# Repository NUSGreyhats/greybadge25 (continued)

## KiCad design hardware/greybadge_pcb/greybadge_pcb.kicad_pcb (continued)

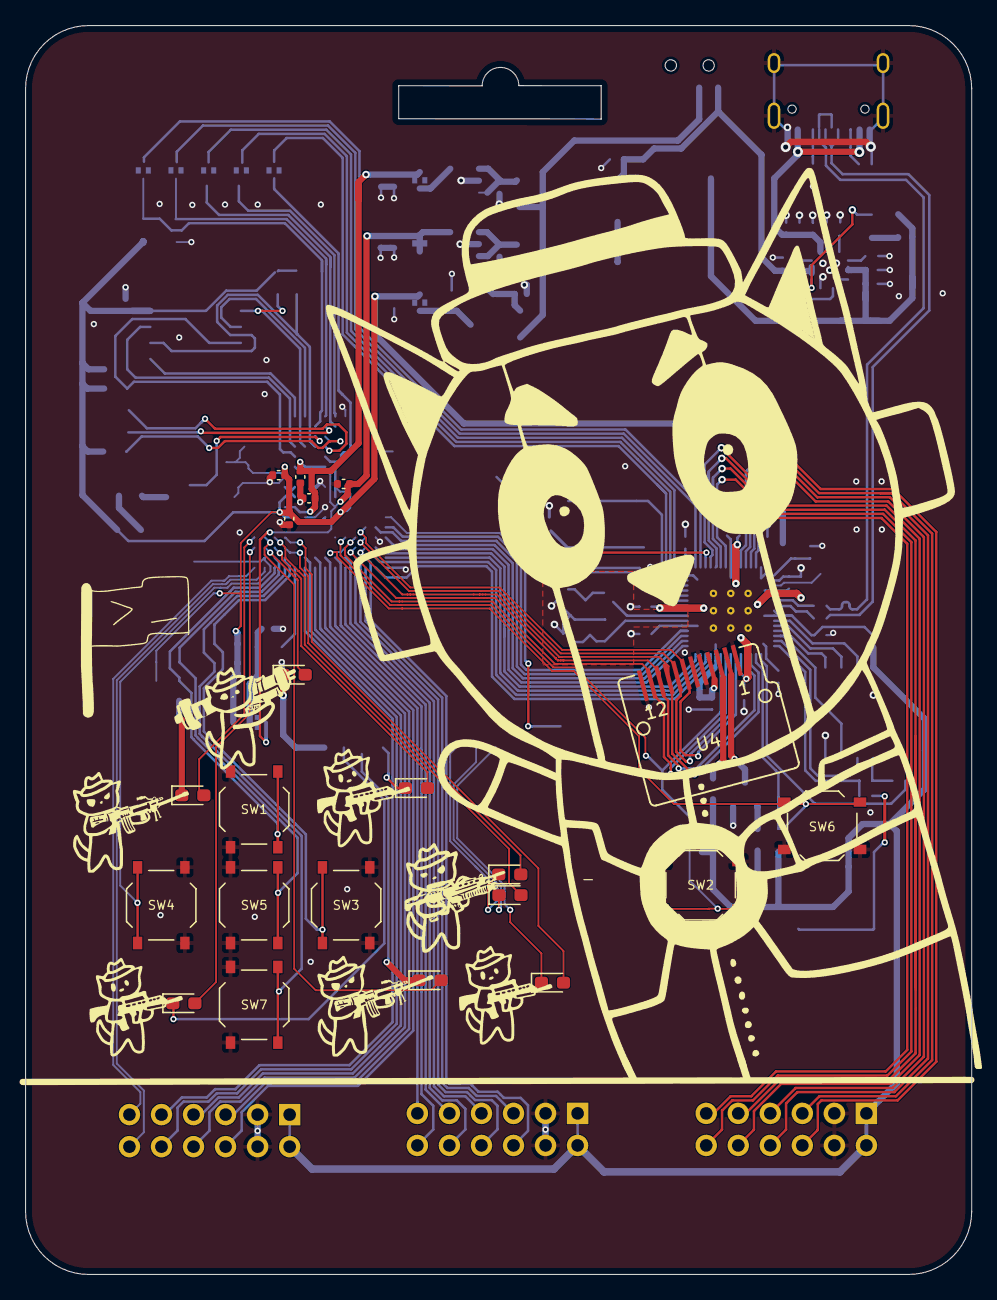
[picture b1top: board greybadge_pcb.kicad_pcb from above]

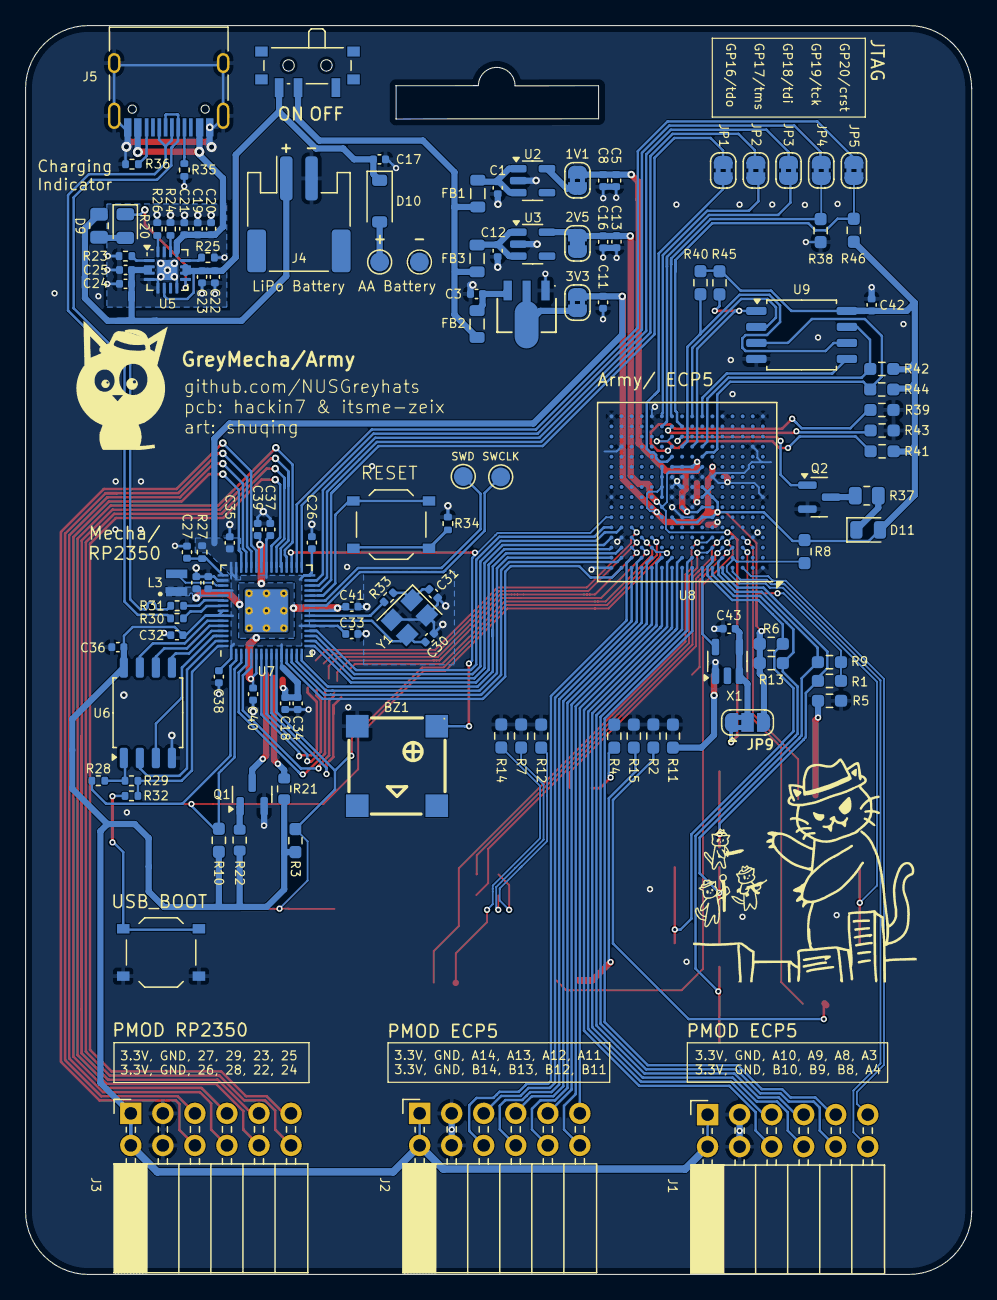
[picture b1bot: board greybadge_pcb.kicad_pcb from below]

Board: 2 copper layers, 75.0 x 99.0 mm, 139 parts (119 on the bottom side), 133 nets.

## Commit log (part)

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2025-02-22 feat: base project
2025-02-22 feat: linking tinyfpga stuff
2025-02-22 feat: arrangement
2025-02-24 Update kicad libs
2025-02-24 Update sch and pcb
2025-03-03 Update routing
2025-03-03 Add screen
2025-03-03 Update routing and zones
2025-03-03 Update routing/zones
2025-03-09 Update fies
2025-03-09 feat: fpga schematic
2025-03-12 feat: rough component placement
2025-03-16 feat: bga and mcu routing
2025-03-16 feat: pcb routing and stuff
2025-03-17 Minor cleanups
2025-03-17 Update badge
2025-03-19 Fix annotation
2025-03-23 feat: leds
2025-03-23 feat: routing cleanupish, power splitting and drc
2025-03-23 feat: played around with jlc bom
2025-03-27 Clean up PCB
2025-03-27 Add file for Bouni JLCPCB plugin
2025-03-28 Update PCB and add JLC files
2025-03-28 Update inductor choice for rp2350
2025-03-28 Minor silkscreen ref update
2025-03-28 Fix 10ohm resistor bom
2025-03-28 Fix 10kohm resistor BOM
2025-03-28 Fix BOM
2025-04-20 Update bom
2025-04-30 Remove LDO and reroute power
2025-05-01 feat: doodlecat
2025-05-01 feat: buzzer etc.
2025-05-01 feat: arms
2025-05-02 Add lipo (wip)
2025-05-07 extend greymecha
2025-05-07 feat: nsf section
2025-05-07 feat: oled move to top sch
2025-05-07 feat: oled to fpga
2025-05-08 feat: artwork positioning i think
2025-05-08 feat: fpga rough verilog
2025-05-08 feat: main fpga project
2025-05-08 feat: circuitpython base
2025-05-08 feat: circup libraries install
2025-05-08 feat: rough sync framework - might make a custom one
2025-05-08 feat: add lipo support
2025-05-08 feat: Add pads for AA batt
2025-05-08 Fix: Use 10k Ohm for R to fix backlight dimming on button press
2025-05-08 Fix: battery/power and clean up silkscreen references
2025-05-08 Update fpga osc to use 2v5
2025-05-08 Add onboard oled (incomplete)
2025-05-08 Update to on-board OLED
2025-05-09 feat: uart sample code
2025-05-09 feat: oled + jtag
2025-05-09 Route buzzer, improve routing/silkscreen ref
2025-05-09 Remove USB LED, add LED charging indicator
2025-05-09 Fix prev commit
2025-05-10 feat: shift button resistors
2025-05-10 feat: base
2025-05-10 feat: basic menu and ui
2025-05-10 feat: chall
2025-05-10 feat: stuff
2025-05-11 Route ADC and power, cleanup routing/silkscreen
2025-05-11 Remove collinear tracks
2025-05-11 Update font sizes
2025-05-11 feat: saf section
2025-05-12 feat: back silkscreen
2025-05-12 feat: to send out?
2025-05-12 Cleanup routing/silkscreen
2025-05-12 Update for ordering
2025-05-12 Fix components
2025-05-14 feat: clown chall
2025-05-14 feat: shooting flag challenge
2025-05-17 feat: uart is painful
2025-05-17 feat: can synthesize but not working
2025-05-17 feat: I think the ticks might work
2025-05-17 feat: baud rate looks working
2025-05-17 feat: i might just have been dumb this whole time
2025-05-17 feat: tx changes state kinda
2025-05-17 feat: uart might be working, it might be an rp2350 issue
2025-05-17 feat: uart works but only for null bytes
2025-05-18 9600 baud rate
2025-05-18 feat: documentation of simple uart
2025-05-18 feat: uart module
2025-05-18 feat: uart flag
2025-05-18 feat: uart receive working
2025-05-18 feat: receive uart working
2025-05-19 art: expert animatar
2025-05-19 art: animations
2025-05-21 chore: cleanup
2025-05-21 Fix: charging indicator
2025-05-22 art: faster and different animations
2025-05-22 feat: fpga modes
2025-05-22 art: mvp attacking
2025-05-23 fix: rp2350 flash
2025-05-23 Fix silkscreen
2025-05-23 art: live firing
2025-05-23 art: new mecha cat
2025-05-23 feat: oscillator power switch
2025-05-23 feat: rp2350 schematic update for flash
2025-05-23 fix: remove excess trace
2025-05-25 art: increase text size
2025-05-25 art: label text width adjustment
2025-05-25 feat: filled ears + removed oscillator mapping
2025-05-25 coloured ears
2025-05-28 cat clownery moment
2025-05-28 updated pcb files with cat clownery
2025-06-01 feat: change oscillator
2025-06-08 minor cleanup + storing mpy files for convenience
2025-06-08 feat: reorg
2025-06-08 feat: new shooting flags infra
2025-06-08 feat: shooting flags is kinda done
2025-06-09 feat: uart verilog that works for rx
2025-06-09 feat: uart rx is somewhat stable?
2025-06-09 feat: uart temp fix - need debug more for sending etc.
2025-06-13 feat: faces cleanup
2025-06-14 feat: secure memory PoC
2025-06-14 feat: major refactoring
2025-06-14 feat: uart bug
2025-06-14 feat: challenge 1
2025-06-15 feat: challenges added
2025-06-15 feat: ctf mode display
2025-06-15 feat: firmware mvp
2025-06-15 Add leaky_gpio25 and restructure challenges
2025-06-15 Move leaky_gpio25 solution
2025-06-15 feat: untested: pmod_j2 chall_secure_mem enable
2025-06-15 Add tetris file
2025-06-19 feat: apparently uart fifo wasnt working this whole time wtf?
2025-06-19 test: uart kinda working on sequence
2025-06-19 feat: sets but doesnt autoclear
2025-06-20 fix: sets (only led[0]), clears, checks packet format
2025-06-20 feat: bruh my math was wrong, it just works now
2025-06-20 reenable uart
2025-06-20 feat: working checkpoint 1
2025-06-20 feat: uart half duplex
2025-06-21 help: logic loops lmao
2025-06-21 feat: uart clean up instruction set
2025-06-21 stuff
2025-06-21 feat: catcore ideation
2025-06-21 module put in but not working properly
2025-06-23 feat: catcore base code structure
2025-06-23 chore: refactoring
2025-06-23 feat: hyper core entrypoint tested
2025-06-23 Fix stdout for leaky_gpio
2025-06-23 Fix: rename gpio22 to gpio25
2025-06-23 feat: catcore hyper somewhat running
2025-06-23 feat: catcore main flag logic
2025-06-23 feat: catcore with LED control
2025-06-23 stuff - so close with the challenge
2025-06-24 some updates eh
2025-06-24 stuff pls help me
2025-06-25 help
2025-06-25 fix: catcore led instruction
2025-06-25 feat: I think i got xor working for admin encryption
2025-06-25 help: theres a short circuit here somewhere, need to fix ASAP
2025-06-25 managed to get that glitching working eh
2025-06-25 feat: Can Change address but just not to what I want huh
2025-06-25 feat: reading from memory works
2025-06-25 address whitelist but not tested?
2025-06-25 feat: challenge FINALLY freaking working somewhat thanks now need documentation
2025-06-25 fix: remove aes and fix heating issue
2025-06-26 Add spoderman rtttl
2025-06-26 slow down shooting flags
2025-06-26 backup
2025-06-26 firmware backup
2025-06-26 update brick game
2025-06-27 Remove challenges from filesystem
2025-06-27 Update clock rate for PIO
2025-06-27 Add uf2 with frozen chall
2025-06-27 features
2025-06-27 feat: animation pause + LED enable
2025-06-27 feat: link author's blog
2025-06-27 Update uf2 (fix leaky for thonny)
2025-06-27 Update uf2 (pid/vid/manu/name)
2025-06-27 feat: CatCore Datasheet
2025-06-27 tetris music
2025-06-27 Update uf2 (Fix hornet revenge)
2025-06-27 Update uf2 (remove hornet revenge)
2025-06-27 hornet revenge fix
2025-06-27 feat: solution
2025-06-27 firmware lock in 1
2025-06-27 mirror tune firmware
2025-06-27 no catcore datasheet
2025-06-27 catcore datasheet
2025-06-27 new datasheet
2025-06-29 Update firmware READMEs
2025-06-29 Add for-fun tetris
2025-06-29 Add initial hardware ordering guide
2025-06-30 Refine README phrasing
2025-07-01 feat: 460800 uart baud rate
2025-07-02 feat: generates bitstream
2025-07-02 simple encryption ?
2025-07-02 proof that aes encryption works
2025-07-02 aes encryption with key is working
2025-07-02 There's hope, THERES HOPE!!!!!!!!
2025-07-02 trigger encryption through UART is working
2025-07-02 its the writing that has issues
2025-07-02 working except for input output
2025-07-02 decryption nonfunctioning groundwork
2025-07-02 even without it, something is overwriting somehwere
2025-07-02 uart in coprocessor fixed
2025-07-02 normal encryption working
2025-07-02 coprocessor is coprocessing?
2025-07-02 rough prototype
2025-07-04 firmware documentation etc.
2025-07-04 brick game update
2025-07-04 asteroids
2025-07-04 sample accelerator test
2025-07-04 feat: lmao spamgame
2025-07-04 spamgame ui fixes
2025-07-04 instruction manual
2025-07-04 coprocessor tidbit
2025-07-05 feat: badapple
